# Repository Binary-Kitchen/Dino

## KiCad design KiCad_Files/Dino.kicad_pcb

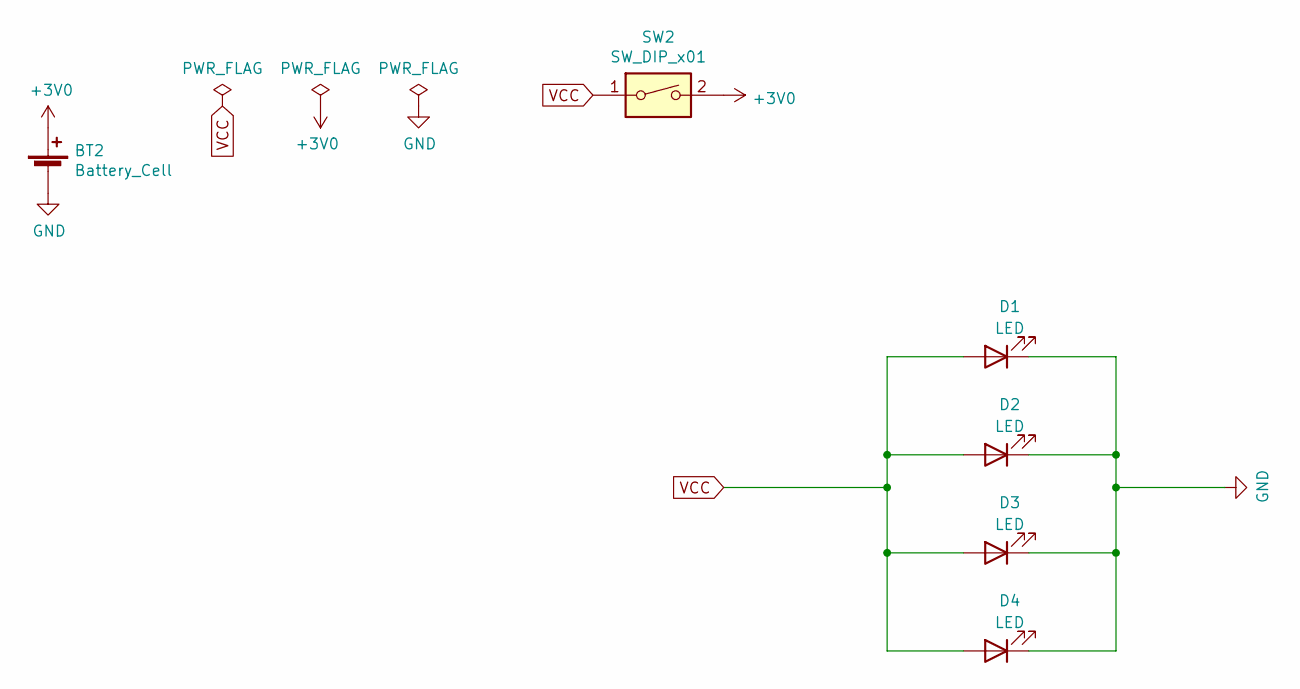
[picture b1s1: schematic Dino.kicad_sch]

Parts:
BT2: Battery_Cell; BatteryHolder_Keystone_1060_1x2032_HandSoldering
D1, D2, D3, D4: LED; 5mm_SMD-Pad
SW2: SW_DIP_x01; Push_Button

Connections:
+3V0: BT2.1 (+), SW2.2
GND: BT2.2 (-), D1.1 (K), D2.1 (K), D3.1 (K), D4.1 (K)
VCC: D1.2 (A), D2.2 (A), D3.2 (A), D4.2 (A), SW2.1

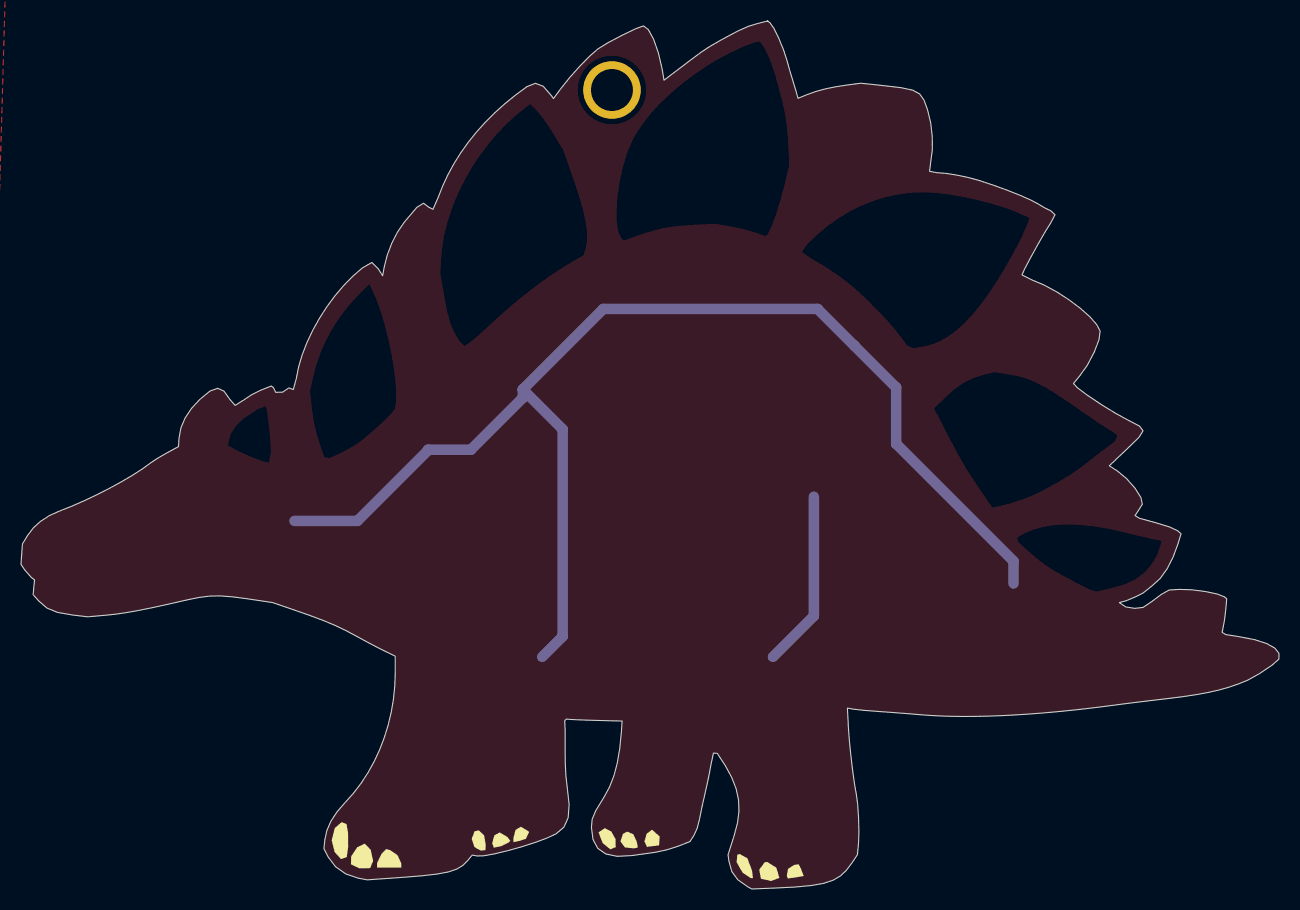
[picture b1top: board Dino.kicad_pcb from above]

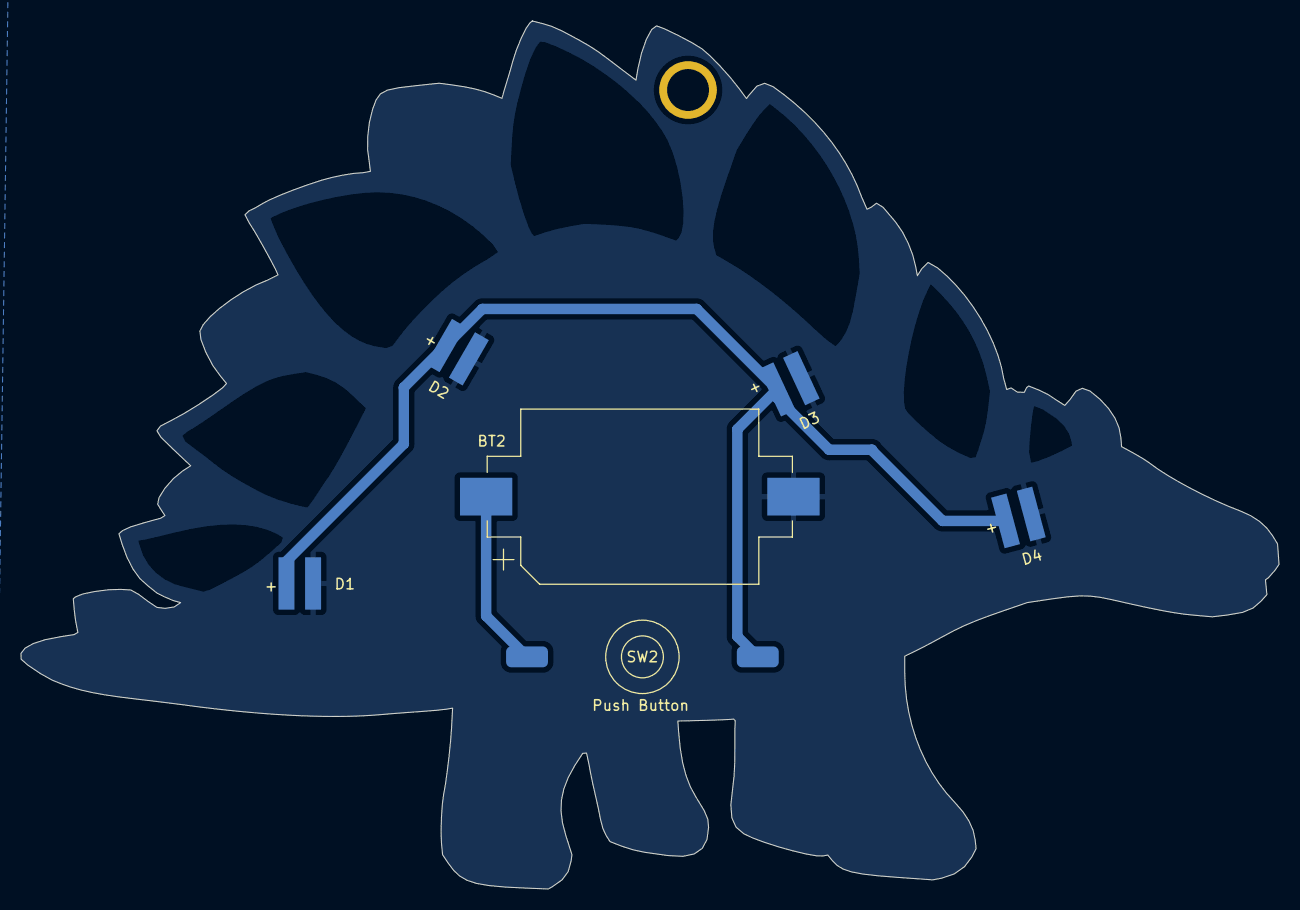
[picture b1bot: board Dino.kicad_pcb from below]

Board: 2 copper layers, 120.0 x 82.8 mm, 7 parts (6 on the bottom side), 3 nets.

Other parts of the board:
svg2mod: G***; dino

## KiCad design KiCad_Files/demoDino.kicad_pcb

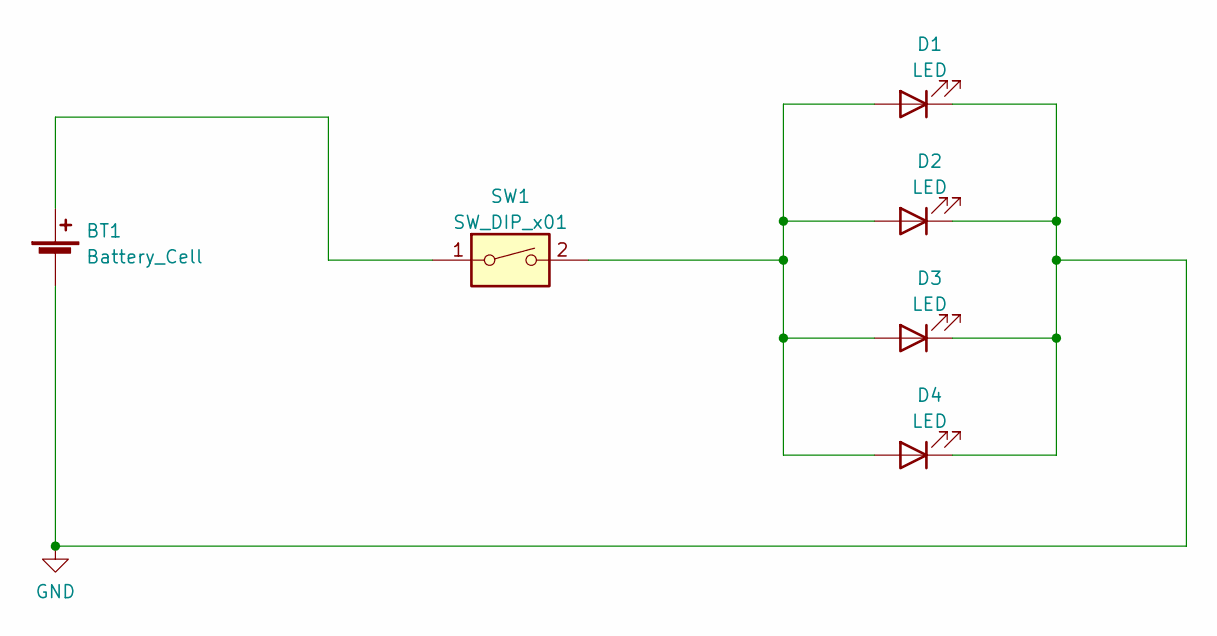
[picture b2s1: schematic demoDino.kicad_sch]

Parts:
BT1: Battery_Cell; BatteryHolder_Keystone_1060_1x2032_HandSoldering
D1, D2, D3, D4: LED; 5mm_SMD-Pad
SW1: SW_DIP_x01; Push_Button

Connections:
unnamed: BT1.2 (-), D1.1 (K), D2.1 (K), D3.1 (K), D4.1 (K)
unnamed: D1.2 (A), D2.2 (A), D3.2 (A), D4.2 (A), SW1.2
unnamed: BT1.1 (+), SW1.1

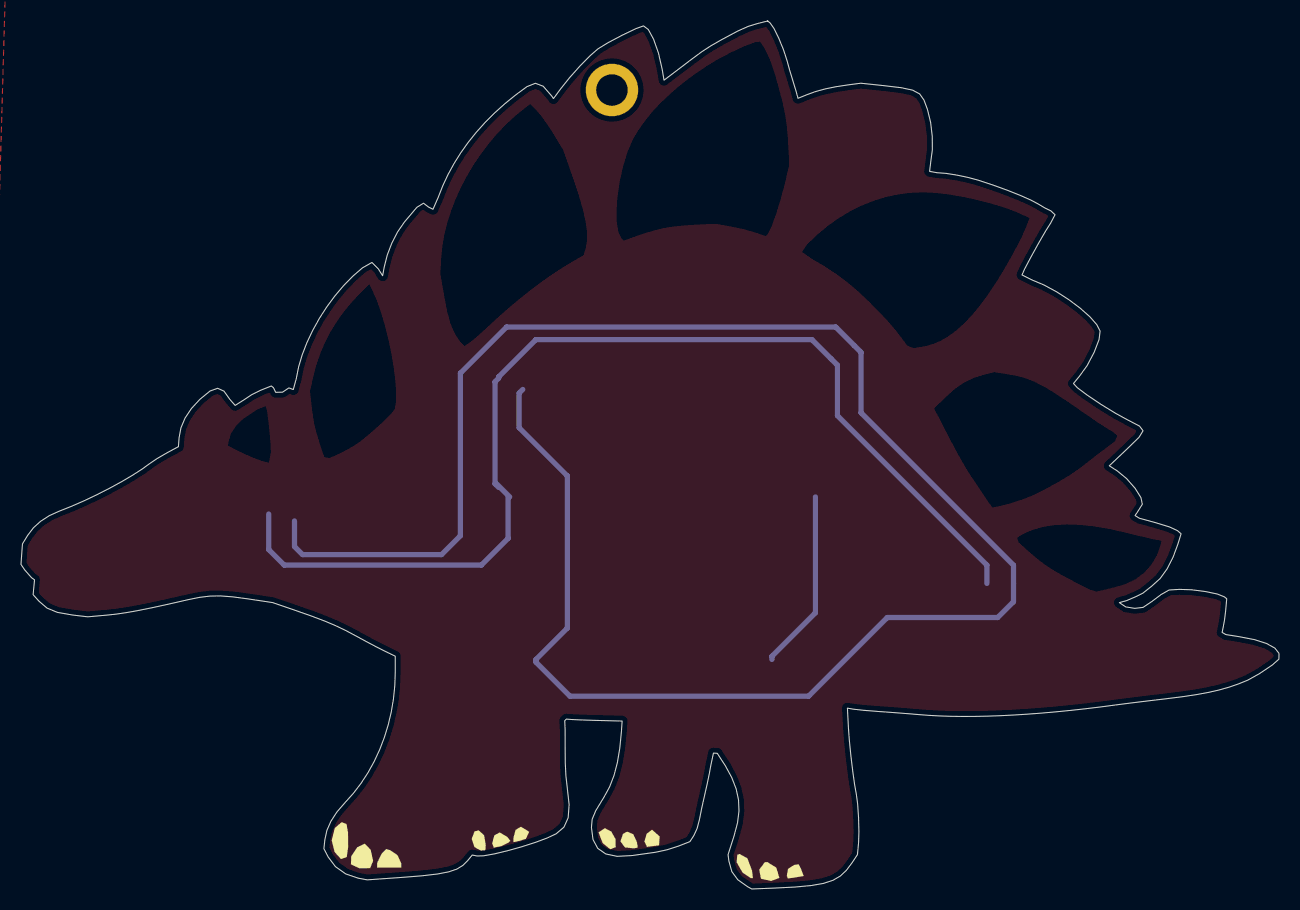
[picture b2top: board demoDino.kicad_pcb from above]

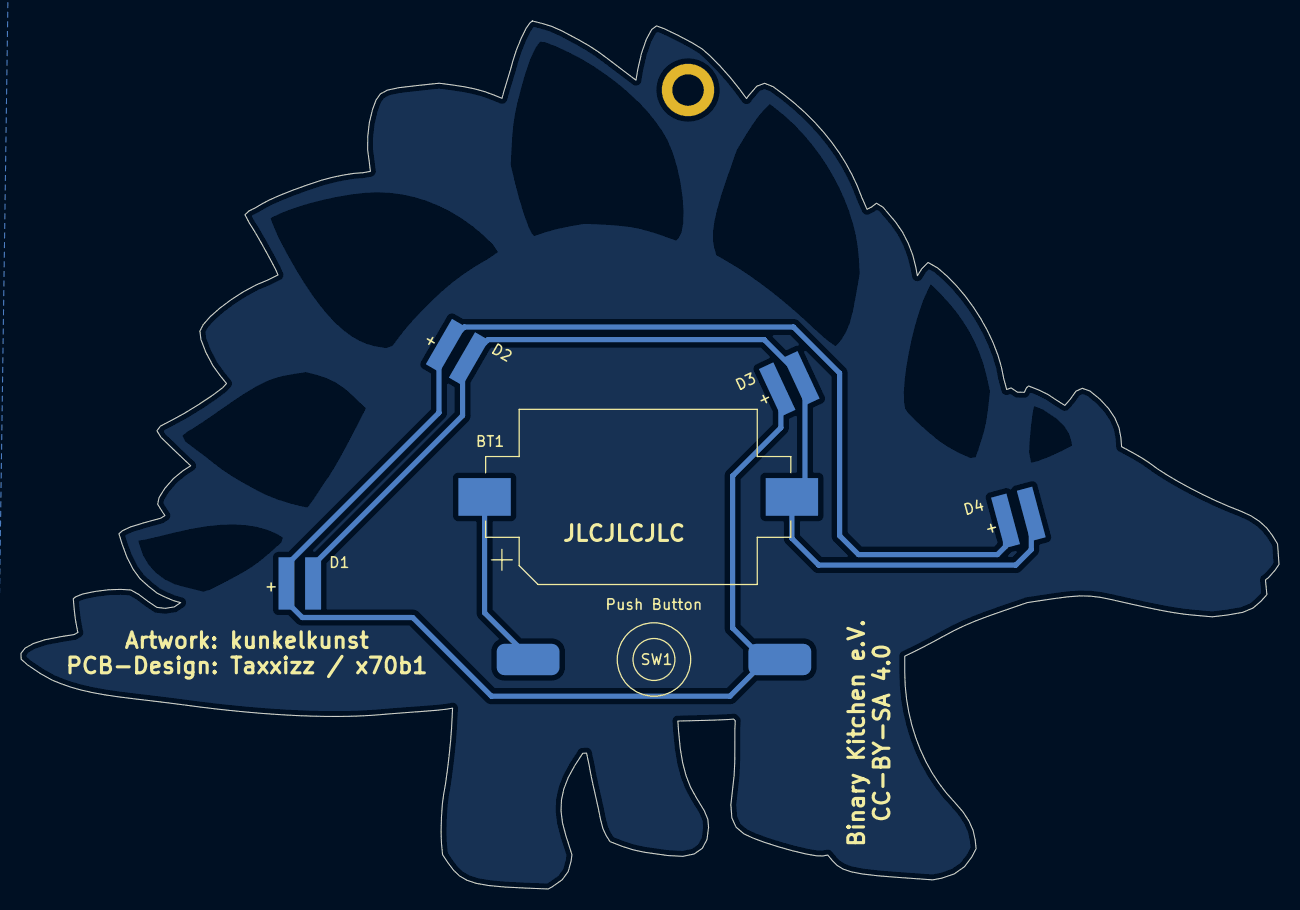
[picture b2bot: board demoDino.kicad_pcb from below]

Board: 2 copper layers, 120.0 x 82.8 mm, 7 parts (6 on the bottom side), 3 nets.

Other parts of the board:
svg2mod: G***; dino

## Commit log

2023-04-19 added kicad specific gitignore
2023-04-19 inital commit sent by taxxis
2023-04-19 deleted not needed files
2023-04-19 added gerber files for 1.0
2023-04-19 renamed files and modified pcb with most recent best practices
2023-04-19 added new footprints
2023-04-19 generated new gerber files for version 1.1
2023-04-19 added ibom

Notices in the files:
KiCad_Files/Dino.kicad_pcb:
CC-BY-SA 4.0
